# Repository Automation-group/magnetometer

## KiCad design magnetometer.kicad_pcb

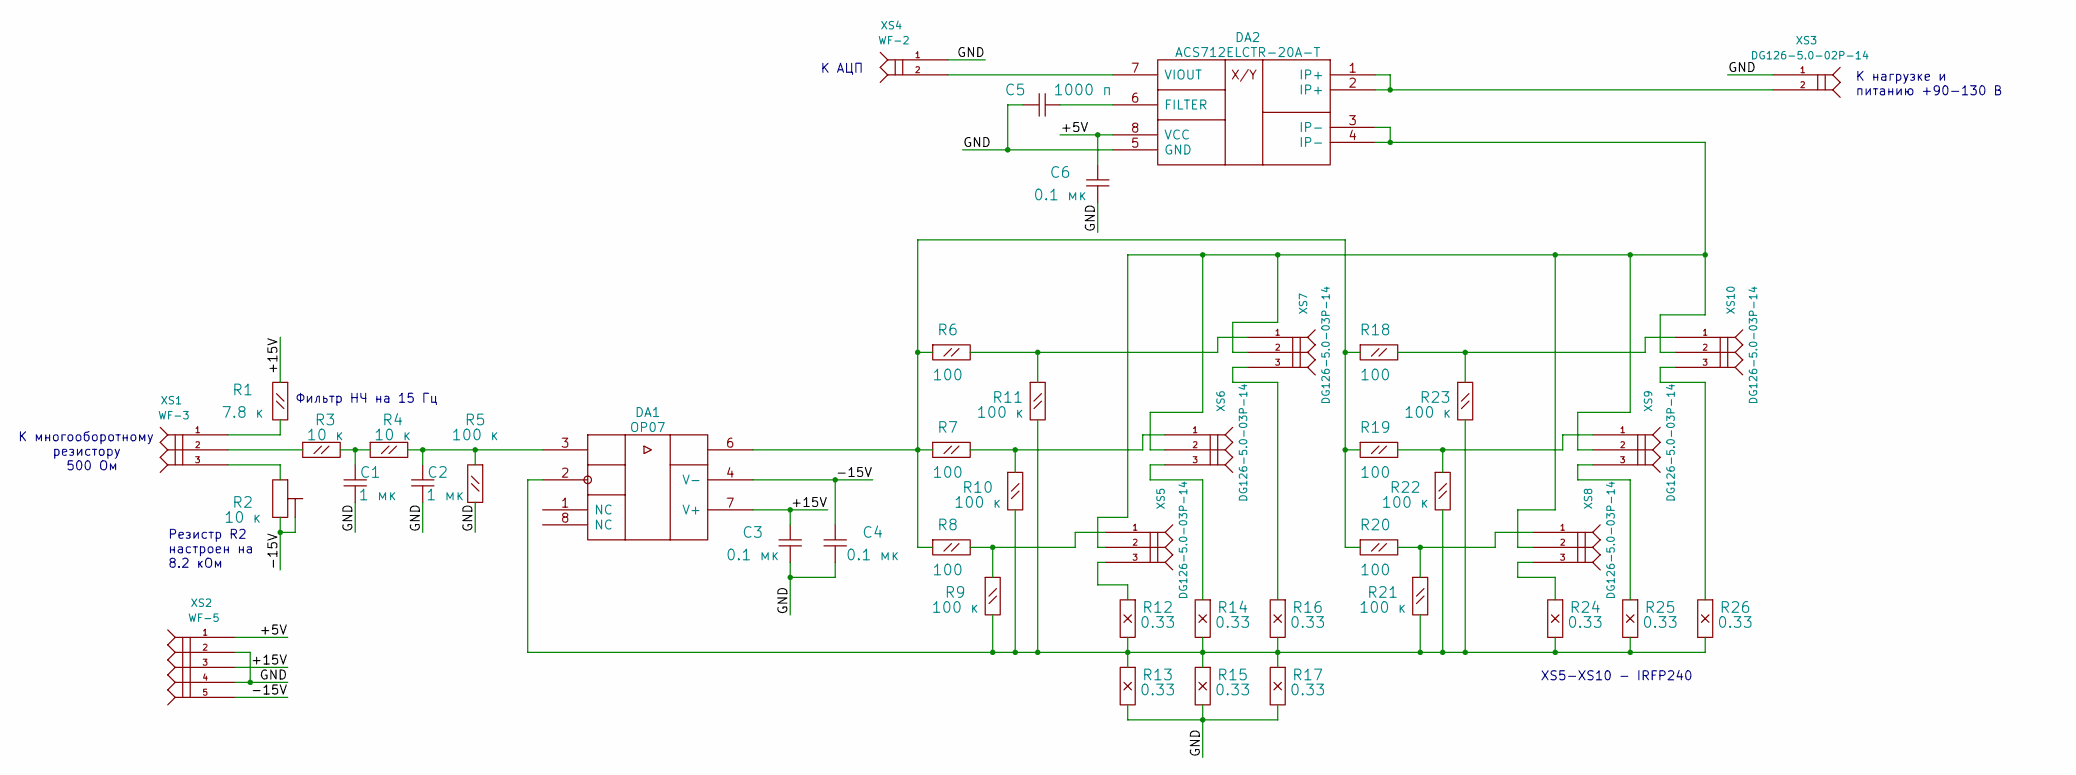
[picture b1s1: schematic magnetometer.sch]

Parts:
C1, C2: 1 мк; SMD0805
C3, C4, C6: 0.1 мк; SMD0805
C5: 1000 п; SMD0805
DA1: OP07; SOIC8
DA2: ACS712ELCTR-20A-T; SOIC8
R1: 7.8 к; RESISTOR_0.25W
R2: 10 к; Electron_3296W
R3, R4: 10 к; RESISTOR_0.25W
R5, R9, R10, R11, R21, R22, R23: 100 к; RESISTOR_0.25W
R6, R7, R8, R18, R19, R20: 100; RESISTOR_0.25W
R12, R13, R14, R15, R16, R17, R24, R25, R26: 0.33; RESISTOR_10W
XS1: WF-3
XS2: WF-5
XS3: DG126-5.0-02P-14
XS4: WF-2
XS5, XS6, XS7, XS8, XS9, XS10: DG126-5.0-03P-14

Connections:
/+5V: C6.1, DA2.8 (VCC), XS2.1
/+15V: C3.1, DA1.7 (V+), R1.1, XS2.3
/-15V: C4.1, DA1.4 (V-), R2.2, R2.3, XS2.5
/GND: C1.2, C2.2, C3.2, C4.2, C5.2, C6.2, DA2.5 (GND), R5.2, R13.2, R15.2, R17.2, XS2.2, XS2.4, XS3.1, XS4.1
unnamed: C1.1, R3.2, R4.1
unnamed: C2.1, DA1.3, R4.2, R5.1
unnamed: C5.1, DA2.6 (FILTER)
unnamed: DA1.2, R9.2, R10.2, R11.2, R12.2, R13.1, R14.2, R15.1, R16.2, R17.1, R21.2, R22.2, R23.2, R24.2, R25.2, R26.2
unnamed: DA1.6, R6.1, R7.1, R8.1, R18.1, R19.1, R20.1
unnamed: DA2.1 (IP+), DA2.2 (IP+), XS3.2
unnamed: DA2.3 (IP-), DA2.4 (IP-), XS5.2, XS6.2, XS7.2, XS8.2, XS9.2, XS10.2
unnamed: DA2.7 (VIOUT), XS4.2
unnamed: R1.2, XS1.1
unnamed: R2.1, XS1.3
unnamed: R3.1, XS1.2
unnamed: R8.2, R9.1, XS5.1
unnamed: R7.2, R10.1, XS6.1
unnamed: R6.2, R11.1, XS7.1
unnamed: R12.1, XS5.3
unnamed: R14.1, XS6.3
unnamed: R16.1, XS7.3
unnamed: R18.2, R23.1, XS10.1
unnamed: R19.2, R22.1, XS9.1
unnamed: R20.2, R21.1, XS8.1
unnamed: R24.1, XS8.3
unnamed: R25.1, XS9.3
unnamed: R26.1, XS10.3

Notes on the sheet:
К нагрузке и питанию +90-130 В
Фильтр НЧ на 15 Гц
Резистр R2 настроен на 8.2 кОм
К многооборотному резистору 500 Ом
К АЦП
XS5-XS10 - IRFP240

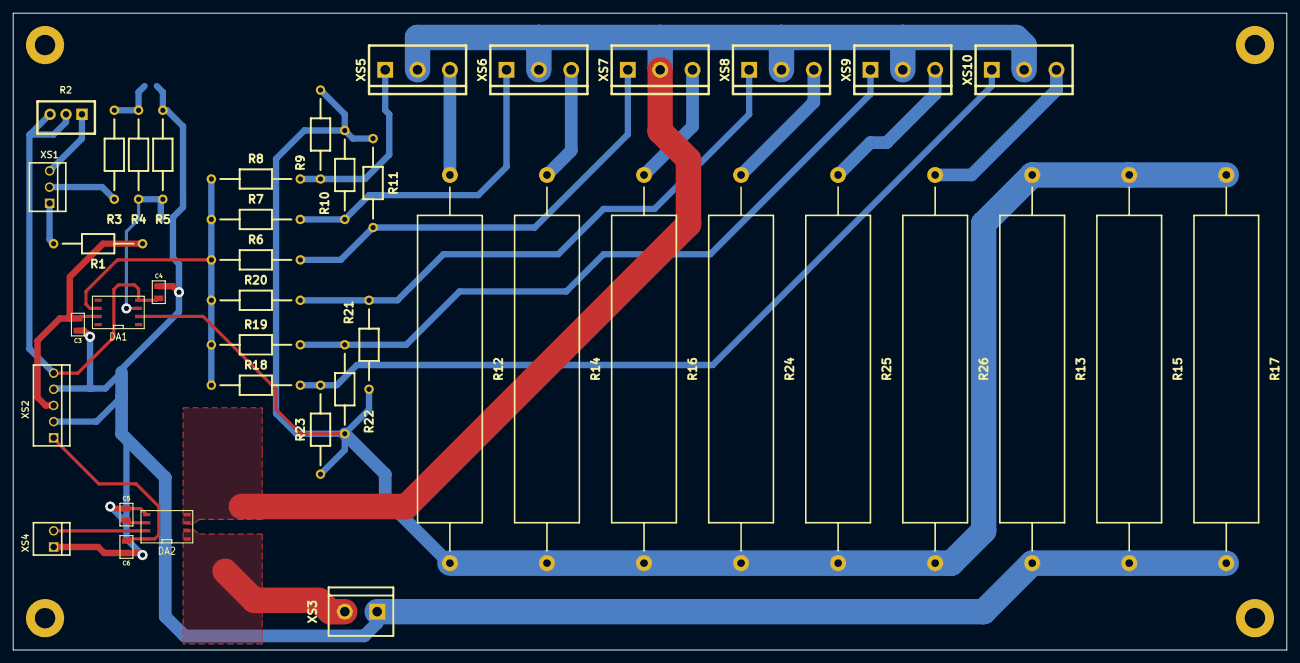
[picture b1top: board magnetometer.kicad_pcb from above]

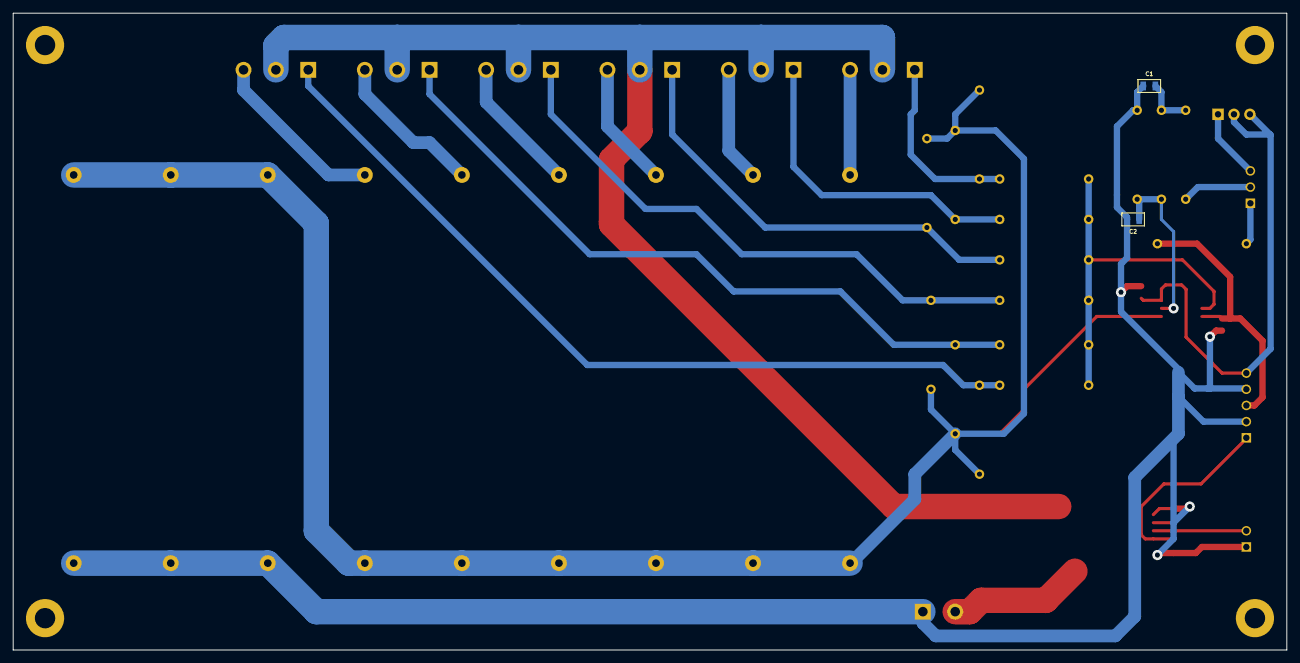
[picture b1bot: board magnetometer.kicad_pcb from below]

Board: 2 copper layers, 200.0 x 100.0 mm, 48 parts (2 on the bottom side), 27 nets.

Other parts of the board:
1_PIN, 1_PIN#2, 1_PIN#3, 1_PIN#4: P***; 1_pin

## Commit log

2017-05-05 -aДобавил схемы источника питания и стабилизатора тока для магнетометра.
2017-05-11 Добавил в схему варистор и поставил автомат защиты напрямую к выводам питания 220В.
2017-06-09 Добавил программу для SafeDuino с АЦП AD7714 и индикаторами.
2019-03-21 Добавил калибровку в программу для амперметра магнитометра.
